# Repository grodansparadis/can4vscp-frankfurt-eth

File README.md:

<h1>CAN4VSCP Frankfurt Eth (PoE)</h1>

This work is based on original work done [here](https://github.com/nuclearcat/ESP32ETH). 

**Frankfurt Eth** is a tcp/ip and MQTT CAN4VSCP gateway. The module is available in two versions. One without PoE and and one with PoE.

The module is plug and play. Just connect to a CAN4VSCP system and go to work. You can connect to the module using [VSCP tcp/ip link protocol](https://grodansparadis.github.io/vscp-doc-spec/#/./vscp_tcpiplink) or set it up to talk to a MQTT broker of choice.

Note that this is **not** a CAN <-> tcp/ip (or MQTT) gateway as it only speaks [VSCP](https://grodansparadis.github.io/vscp-doc-spec). It is possible though to load firmware into it to create a standard CAN (not CAN FD) <-> tcp/ip gateway. 

The project uses an ESP32 Wroom module. It utilize Ethernet instead of Wifi/Bluetooth. Ethernet interface is provided with a LAN8720A and CAN is provided by the ESP32 support for TWAI. The module is powered from the [CAN4VSCP bus](https://grodansparadis.github.io/vscp-doc-spec/#/./vscp_over_can_can4vscp) (or PoE).  When powered from PoE the module can provide power for other CAN4VSCP modules. CAN4VSCP power is in the range +9V - 28V.

The intended use is to connect a remote CAN4VSCP bus to a central system or to connect two or more CAN4VSCP networks together. 

If Wifi is required instead of Ethernet the [CAN4VSCP Frankfurt Wifi module](https://github.com/grodansparadis/can4vscp-frankfurt-wifi) is available that can do that.

Prototype PCB's for this project has been sponsored by [PCBWay](https://www.pcbway.com/). We can really recommend this service if you need high quality PCB's. 

## Schema

### Standard version

### PoE version

## Standard version

## PoE Version

<hr>
Please support the <a href="http://www.vscp.org">VSCP development</a>. The best way to support the project is 
to buy something from the <a href="http://www.frogshop.se">FrogShop</a>. If you want to contribute money use the button
 at the end of the <a href="http://www.vscp.org">VSCP sites</a> start page.

Visit our <a href="http://www.vscp.org/wiki/doku.php/sponsors">sponsor page</a> for all options.

<hr>

Part of the VSCP Project.

Copyright 2018-2026 © Åke Hedman, (Grodans Paradis AB)[https://www.grodansparadis.com]

<hr>

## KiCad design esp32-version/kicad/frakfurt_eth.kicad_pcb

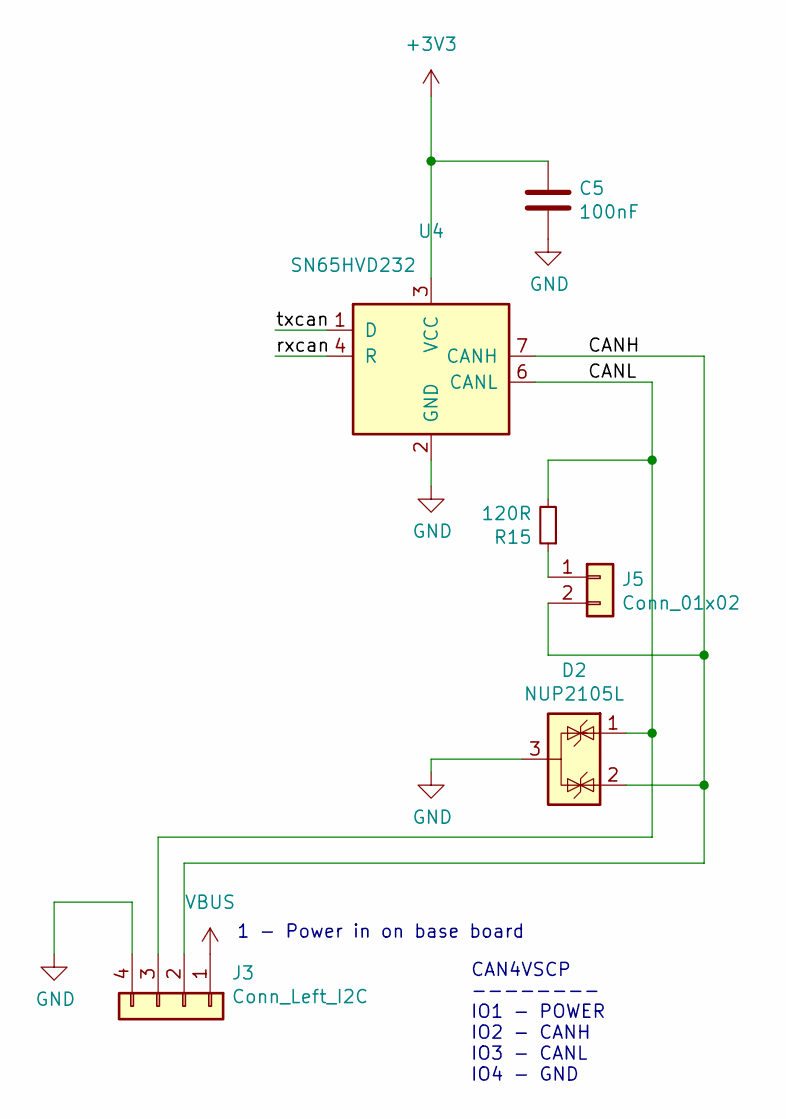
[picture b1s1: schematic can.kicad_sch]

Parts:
C5: 100nF; C_0805_2012Metric
D2: NUP2105L; SOT-23
J3: Conn_Left_I2C; PinHeader_1x04_P2.54mm_Vertical
J5: Conn_01x02; PinHeader_1x02_P2.54mm_Vertical
R15: 120R; R_0805_2012Metric
U4: SN65HVD232; SOIC-8_3.9x4.9mm_P1.27mm

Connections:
/CANH: D2.2 (K), J3.2, J5.2, U4.7 (CANH); also elsewhere on the board
/CANL: D2.1 (K), J3.3, R15.2, U4.6 (CANL); also elsewhere on the board
/rxcan: U4.4 (R); also elsewhere on the board
/txcan: U4.1 (D); also elsewhere on the board
GND: C5.2, D2.3 (A), J3.4, U4.2 (GND); also elsewhere on the board
unnamed: J5.1, R15.1

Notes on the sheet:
1 - Power in on base board
CAN4VSCP -------- IO1 - POWER IO2 - CANH IO3 - CANL IO4 - GND

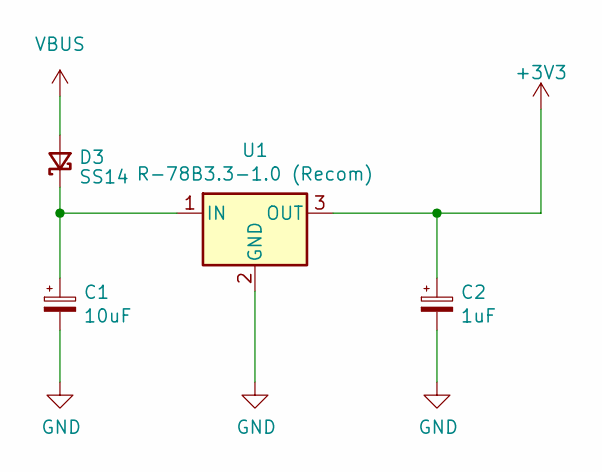
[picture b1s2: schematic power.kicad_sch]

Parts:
C1: 10uF; C_0805_2012Metric_Pad1.18x1.45mm_HandSolder
C2: 1uF; C_0805_2012Metric_Pad1.18x1.45mm_HandSolder
D3: SS14; D_SMA
U1: R-78B3.3-1.0 (Recom); Converter_DCDC_RECOM_R-78B-2.0_THT

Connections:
unnamed: C1.2, C2.2, U1.2 (GND)
unnamed: C2.1, U1.3 (OUT)
unnamed 31: C1.1, D3.1 (K), U1.1 (IN); also elsewhere on the board
VBUS: D3.2 (A); also elsewhere on the board

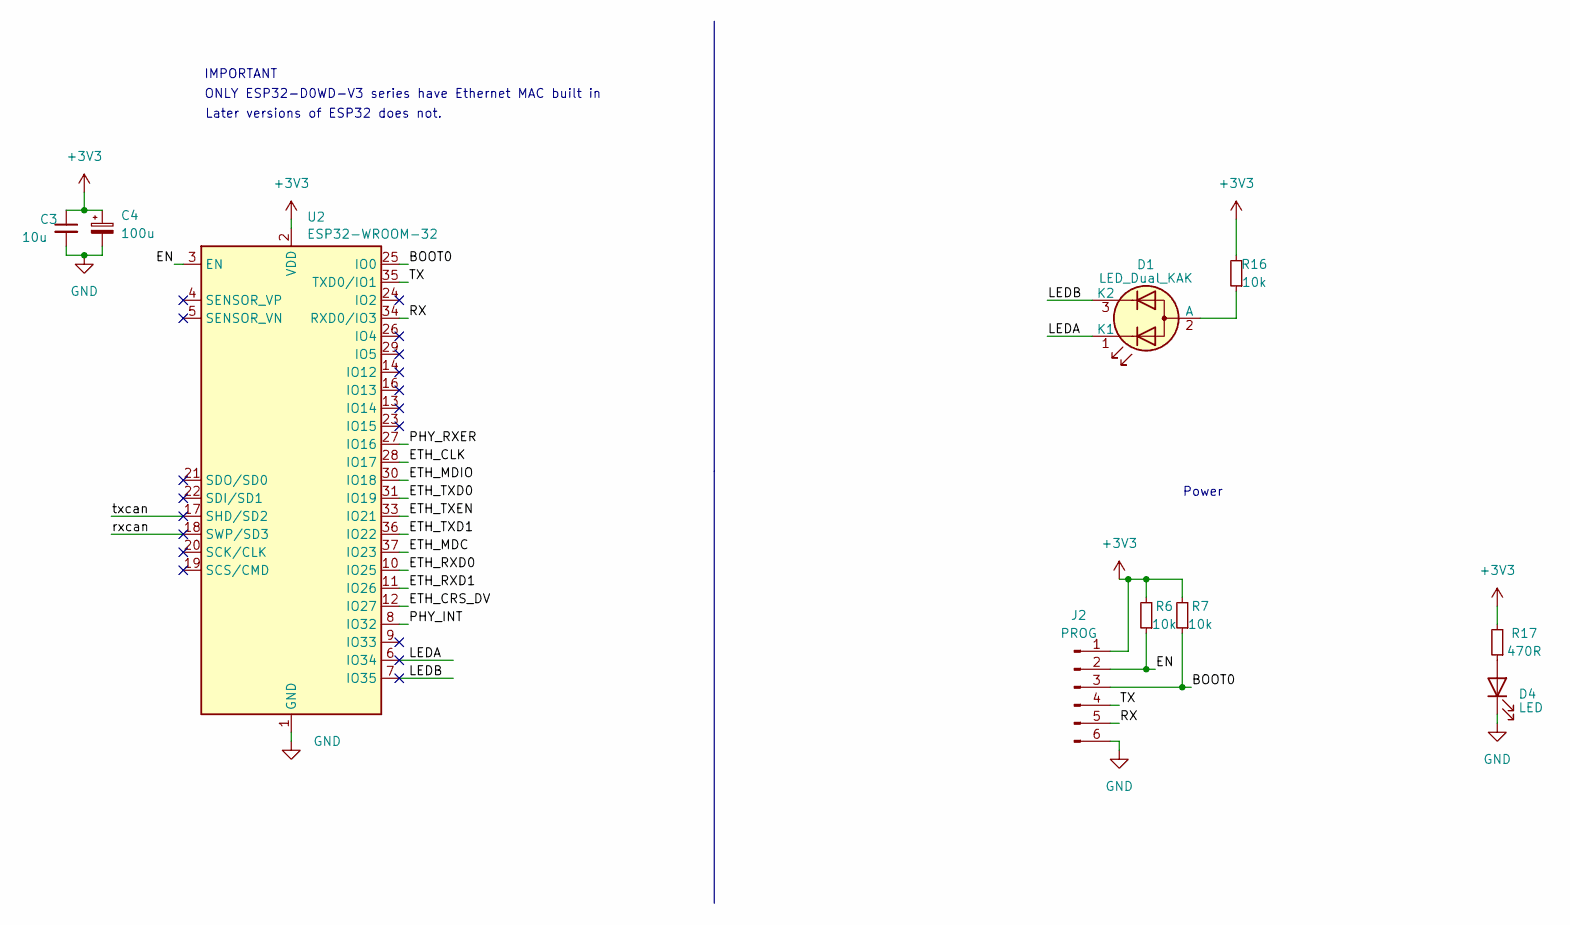
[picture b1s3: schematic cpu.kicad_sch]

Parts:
C3: 10u; C_0805_2012Metric_Pad1.18x1.45mm_HandSolder
C4: 100u; CP_EIA-3528-21_Kemet-B
D1: LED_Dual_KAK; LED_D5.0mm-3
D4: LED; LED_0805_2012Metric_Pad1.15x1.40mm_HandSolder
J2: PROG; PinHeader_1x06_P2.54mm_Vertical
R6, R7, R16: 10k; R_0805_2012Metric_Pad1.20x1.40mm_HandSolder
R17: 470R; R_0805_2012Metric_Pad1.20x1.40mm_HandSolder
U2: ESP32-WROOM-32

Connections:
/BOOT0: J2.3, R7.1, U2.25 (IO0)
/EN: J2.2, R6.1, U2.3 (EN)
/ETH_CLK: U2.28 (IO17); also elsewhere on the board
/ETH_CRS_DV: U2.12 (IO27); also elsewhere on the board
/ETH_MDC: U2.37 (IO23); also elsewhere on the board
/ETH_MDIO: U2.30 (IO18); also elsewhere on the board
/ETH_RXD0: U2.10 (IO25); also elsewhere on the board
/ETH_RXD1: U2.11 (IO26); also elsewhere on the board
/ETH_TXD0: U2.31 (IO19); also elsewhere on the board
/ETH_TXD1: U2.36 (IO22); also elsewhere on the board
/ETH_TXEN: U2.33 (IO21); also elsewhere on the board
/LEDA: D1.1 (K1), U2.6 (IO34)
/LEDB: D1.3 (K2), U2.7 (IO35)
/PHY_INT: U2.8 (IO32); also elsewhere on the board
/PHY_RXER: U2.27 (IO16); also elsewhere on the board
/RX: J2.5, U2.34 (RXD0/IO3)
/TX: J2.4, U2.35 (TXD0/IO1)
/rxcan: U2.18 (SWP/SD3); also elsewhere on the board
/txcan: U2.17 (SHD/SD2); also elsewhere on the board
GND: C3.2, C4.2, D4.1 (K), J2.6, U2.1 (GND), U2.15 (GND), U2.38 (GND), U2.39 (GND); also elsewhere on the board
unnamed: D1.2 (A), R16.1
unnamed: D4.2 (A), R17.1

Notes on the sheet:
Later versions of ESP32 does not.
ONLY ESP32-D0WD-V3 series have Ethernet MAC built in
IMPORTANT
Power

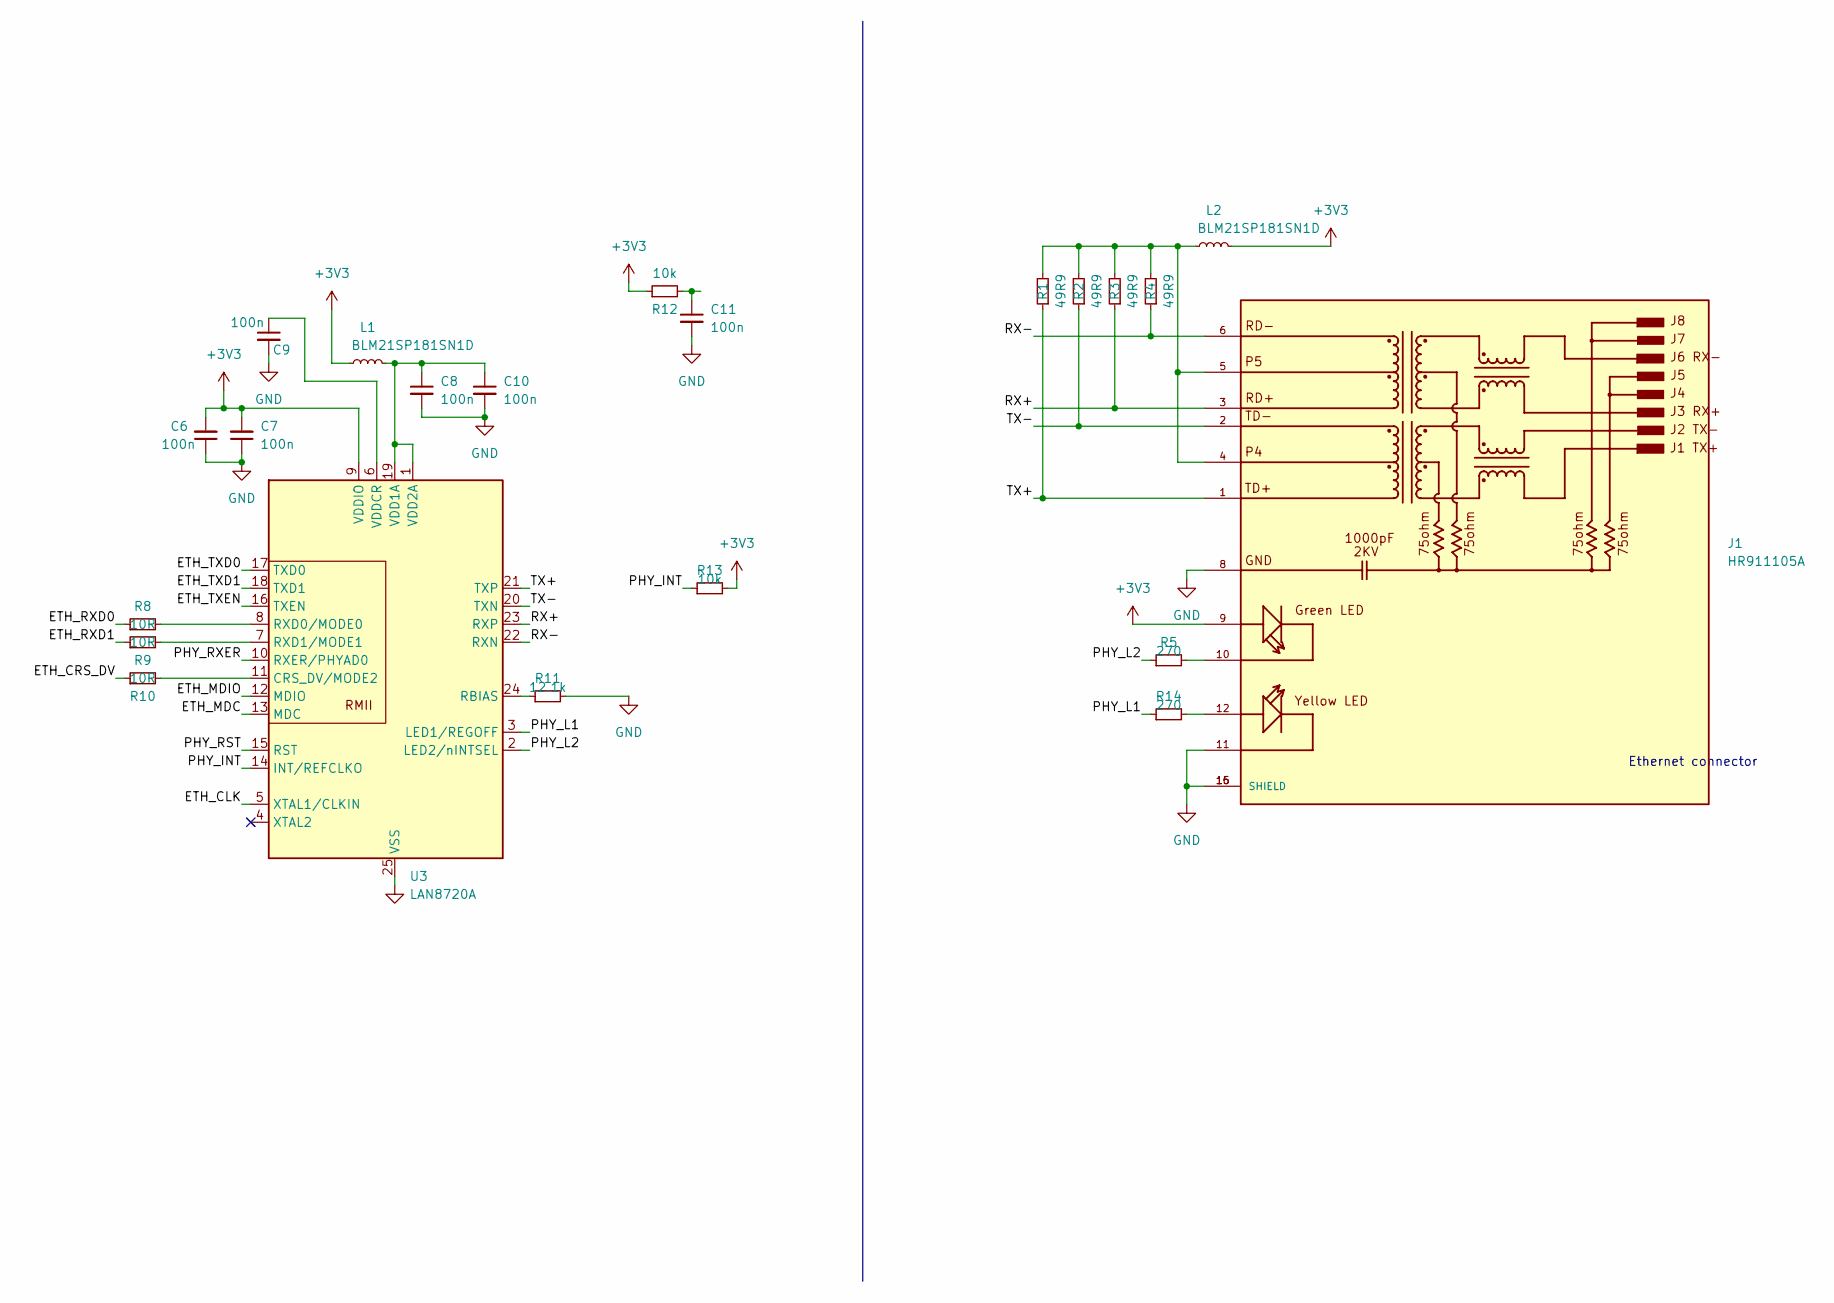
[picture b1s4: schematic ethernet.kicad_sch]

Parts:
C6, C7, C8, C9, C10, C11: 100n; C_0805_2012Metric_Pad1.18x1.45mm_HandSolder
J1: HR911105A; HANRUN_HR911105A; PARTREV A
L1, L2: BLM21SP181SN1D; R_0805_2012Metric_Pad1.20x1.40mm_HandSolder
R1, R2, R3, R4: 49R9; R_0805_2012Metric_Pad1.20x1.40mm_HandSolder
R5, R14: 270; R_0805_2012Metric_Pad1.20x1.40mm_HandSolder
R8, R9, R10: 10R; R_0805_2012Metric_Pad1.20x1.40mm_HandSolder
R11: 12.1k; R_0805_2012Metric_Pad1.20x1.40mm_HandSolder
R12, R13: 10k; R_0805_2012Metric_Pad1.20x1.40mm_HandSolder
U3: LAN8720A; QFN-24-1EP_4x4mm_P0.5mm_EP2.6x2.6mm

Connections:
/ETH_CLK: U3.5 (XTAL1/CLKIN); also elsewhere on the board
/ETH_CRS_DV: R10.1; also elsewhere on the board
/ETH_MDC: U3.13 (MDC); also elsewhere on the board
/ETH_MDIO: U3.12 (MDIO); also elsewhere on the board
/ETH_RXD0: R8.1; also elsewhere on the board
/ETH_RXD1: R9.1; also elsewhere on the board
/ETH_TXD0: U3.17 (TXD0); also elsewhere on the board
/ETH_TXD1: U3.18 (TXD1); also elsewhere on the board
/ETH_TXEN: U3.16 (TXEN); also elsewhere on the board
/PHY_INT: R13.1, U3.14 (INT/REFCLKO); also elsewhere on the board
/PHY_L1: R14.1, U3.3 (LED1/REGOFF)
/PHY_L2: R5.1, U3.2 (LED2/nINTSEL)
/PHY_RXER: U3.10 (RXER/PHYAD0); also elsewhere on the board
/RX+: J1.3, R3.1, U3.23 (RXP)
/RX-: J1.6, R4.1, U3.22 (RXN)
/TX+: J1.1, R1.1, U3.21 (TXP)
/TX-: J1.2, R2.1, U3.20 (TXN)
GND: C6.1, C7.1, C8.2, C9.2, C10.2, C11.2, J1.8, J1.11, J1.15 (SHIELD), J1.16 (SHIELD), R11.2, U3.25 (VSS); also elsewhere on the board
unnamed: J1.10, R5.2
unnamed: J1.12, R14.2
unnamed: R10.2, U3.11 (CRS_DV/MODE2)
unnamed: R11.1, U3.24 (RBIAS)
unnamed: R8.2, U3.8 (RXD0/MODE0)
unnamed: R9.2, U3.7 (RXD1/MODE1)
unnamed: C8.1, C10.1, L1.2, U3.1 (VDD2A), U3.19 (VDD1A)
unnamed: C9.1, U3.6 (VDDCR)

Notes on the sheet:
Ethernet connector

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
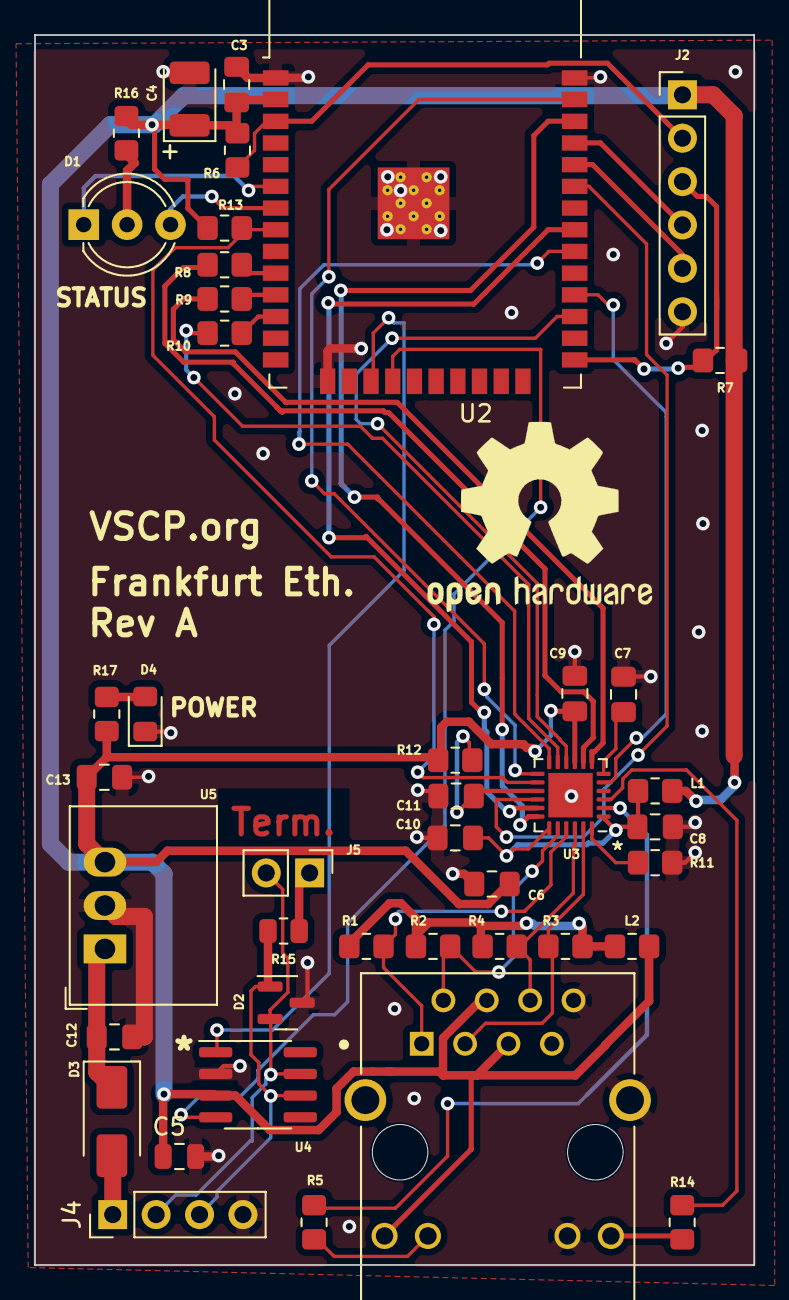
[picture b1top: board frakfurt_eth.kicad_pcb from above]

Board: 2 copper layers, 42.1 x 72.0 mm, 42 parts (0 on the bottom side), 44 nets.

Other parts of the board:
C12: 10uF; C_0805_2012Metric_Pad1.18x1.45mm_HandSolder
C13: 1uF; C_0805_2012Metric_Pad1.18x1.45mm_HandSolder
J4: Conn_Left_I2C; PinHeader_1x04_P2.54mm_Vertical
U5: R-78B3.3-1.0 (Recom); Converter_DCDC_RECOM_R-78B-2.0_THT

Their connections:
/CANH: J4.2; also elsewhere on the board
/CANL: J4.3; also elsewhere on the board
GND: C12.2, C13.2, J4.4, U5.2 (GND); also elsewhere on the board
unnamed 31: C12.1, U5.1 (IN); also elsewhere on the board
VBUS: J4.1; also elsewhere on the board

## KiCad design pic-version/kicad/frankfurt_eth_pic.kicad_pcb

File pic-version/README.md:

# Microchip PIC Version

This is an old version of this project that is no longer maintained.

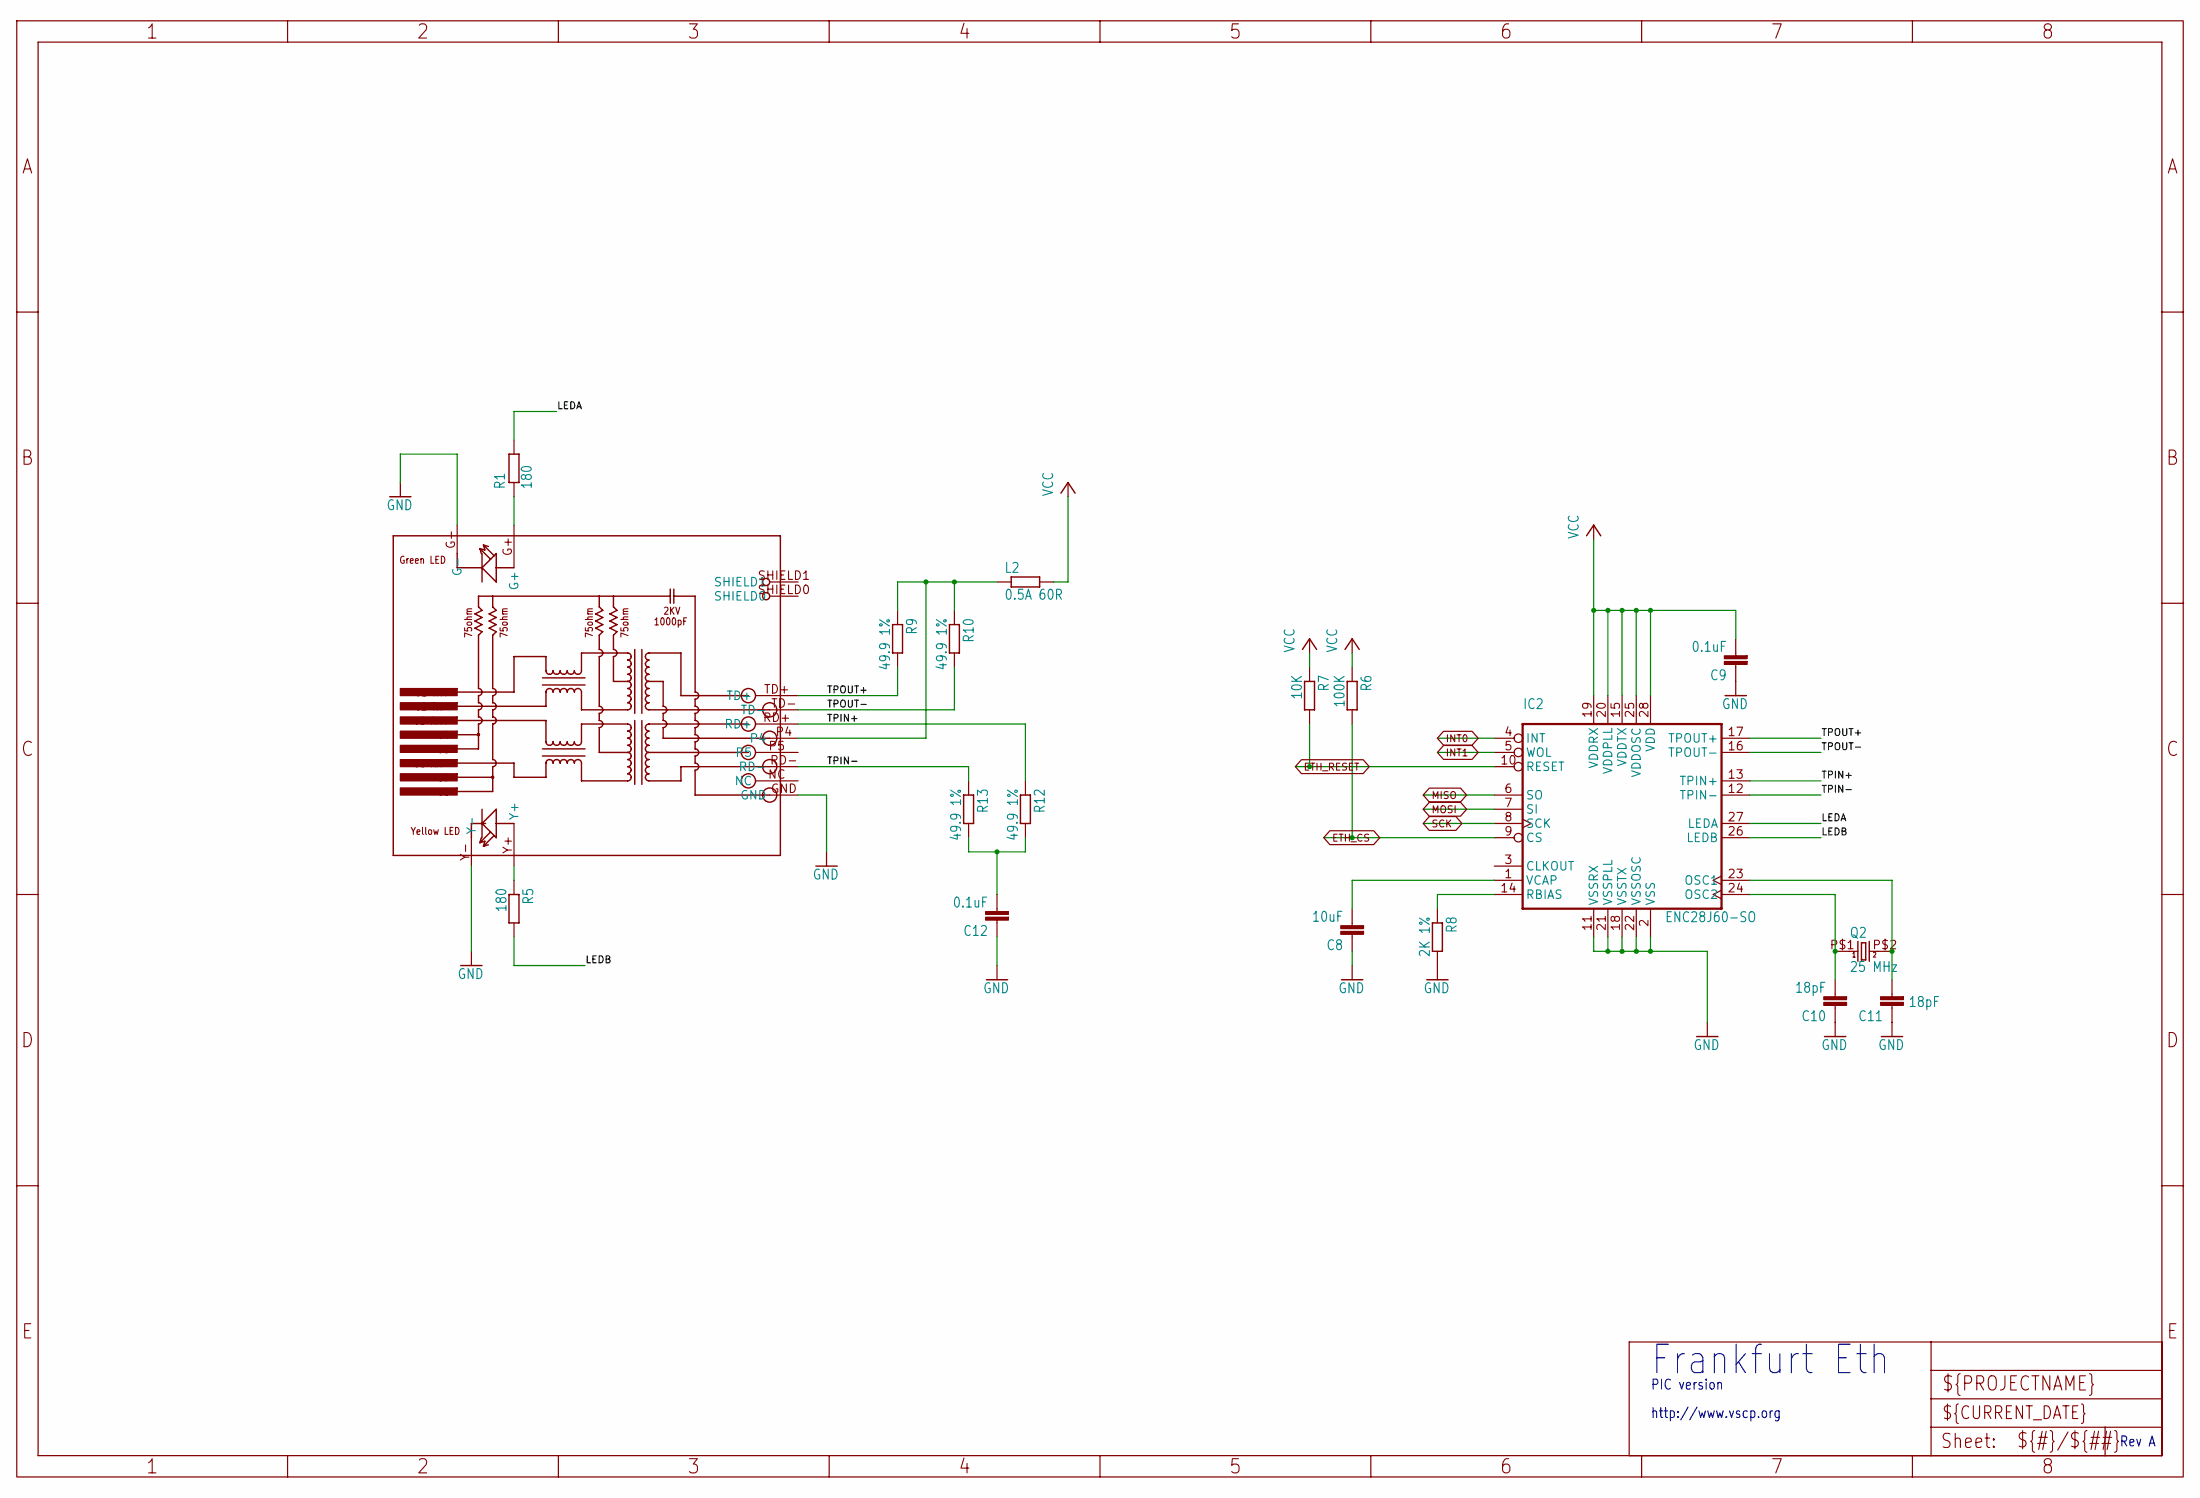
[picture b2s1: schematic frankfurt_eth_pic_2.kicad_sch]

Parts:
C8: 10uF; C0805
C9, C12: 0.1uF; C0805
C10, C11: 18pF; C0805
IC2: ENC28J60-SO; SO28W
L2: 0.5A 60R; R0805
Q2: 25 MHz; 9C
R1, R5: 180; R0805
R6: 100K; R0805
R7: 10K; R0805
R8: 2K 1%; R0805
R9, R10, R12, R13: 49.9 1%; R0805
RJ1: HR911105A

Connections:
ETH_CS: IC2.9 (CS), R6.2; also elsewhere on the board
ETH_RESET: IC2.10 (RESET), R7.2; also elsewhere on the board
GND: C8.1, C9.1, C10.1, C11.1, C12.1, IC2.2 (VSS), IC2.11 (VSSRX), IC2.18 (VSSTX), IC2.21 (VSSPLL), IC2.22 (VSSOSC), R8.2, RJ1.G-, RJ1.GND, RJ1.Y-; also elsewhere on the board
INT0: IC2.4 (INT); also elsewhere on the board
INT1: IC2.5 (WOL); also elsewhere on the board
LEDA: IC2.27 (LEDA), R1.2
LEDB: IC2.26 (LEDB), R5.2
MISO: IC2.6 (SO); also elsewhere on the board
MOSI: IC2.7 (SI); also elsewhere on the board
unnamed: R1.1, RJ1.G+
unnamed: C8.2, IC2.1 (VCAP)
unnamed: R5.1, RJ1.Y+
unnamed: IC2.14 (RBIAS), R8.1
unnamed: C10.2, IC2.24 (OSC2), Q2.P$1 (1)
unnamed: C11.2, IC2.23 (OSC1), Q2.P$2 (2)
unnamed: C12.2, R12.2, R13.2
unnamed: L2.1, R9.1, R10.1, RJ1.P4
SCK: IC2.8 (SCK); also elsewhere on the board
TPIN+: IC2.13 (TPIN+), R12.1, RJ1.RD+
TPIN-: IC2.12 (TPIN-), R13.1, RJ1.RD-
TPOUT+: IC2.17 (TPOUT+), R9.2, RJ1.TD+
TPOUT-: IC2.16 (TPOUT-), R10.2, RJ1.TD-
VCC: C9.2, IC2.15 (VDDTX), IC2.19 (VDDRX), IC2.20 (VDDPLL), IC2.25 (VDDOSC), IC2.28 (VDD), L2.2, R6.1, R7.1; also elsewhere on the board

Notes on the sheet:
Rev A
Frankfurt Eth
PIC version
http://www.vscp.org

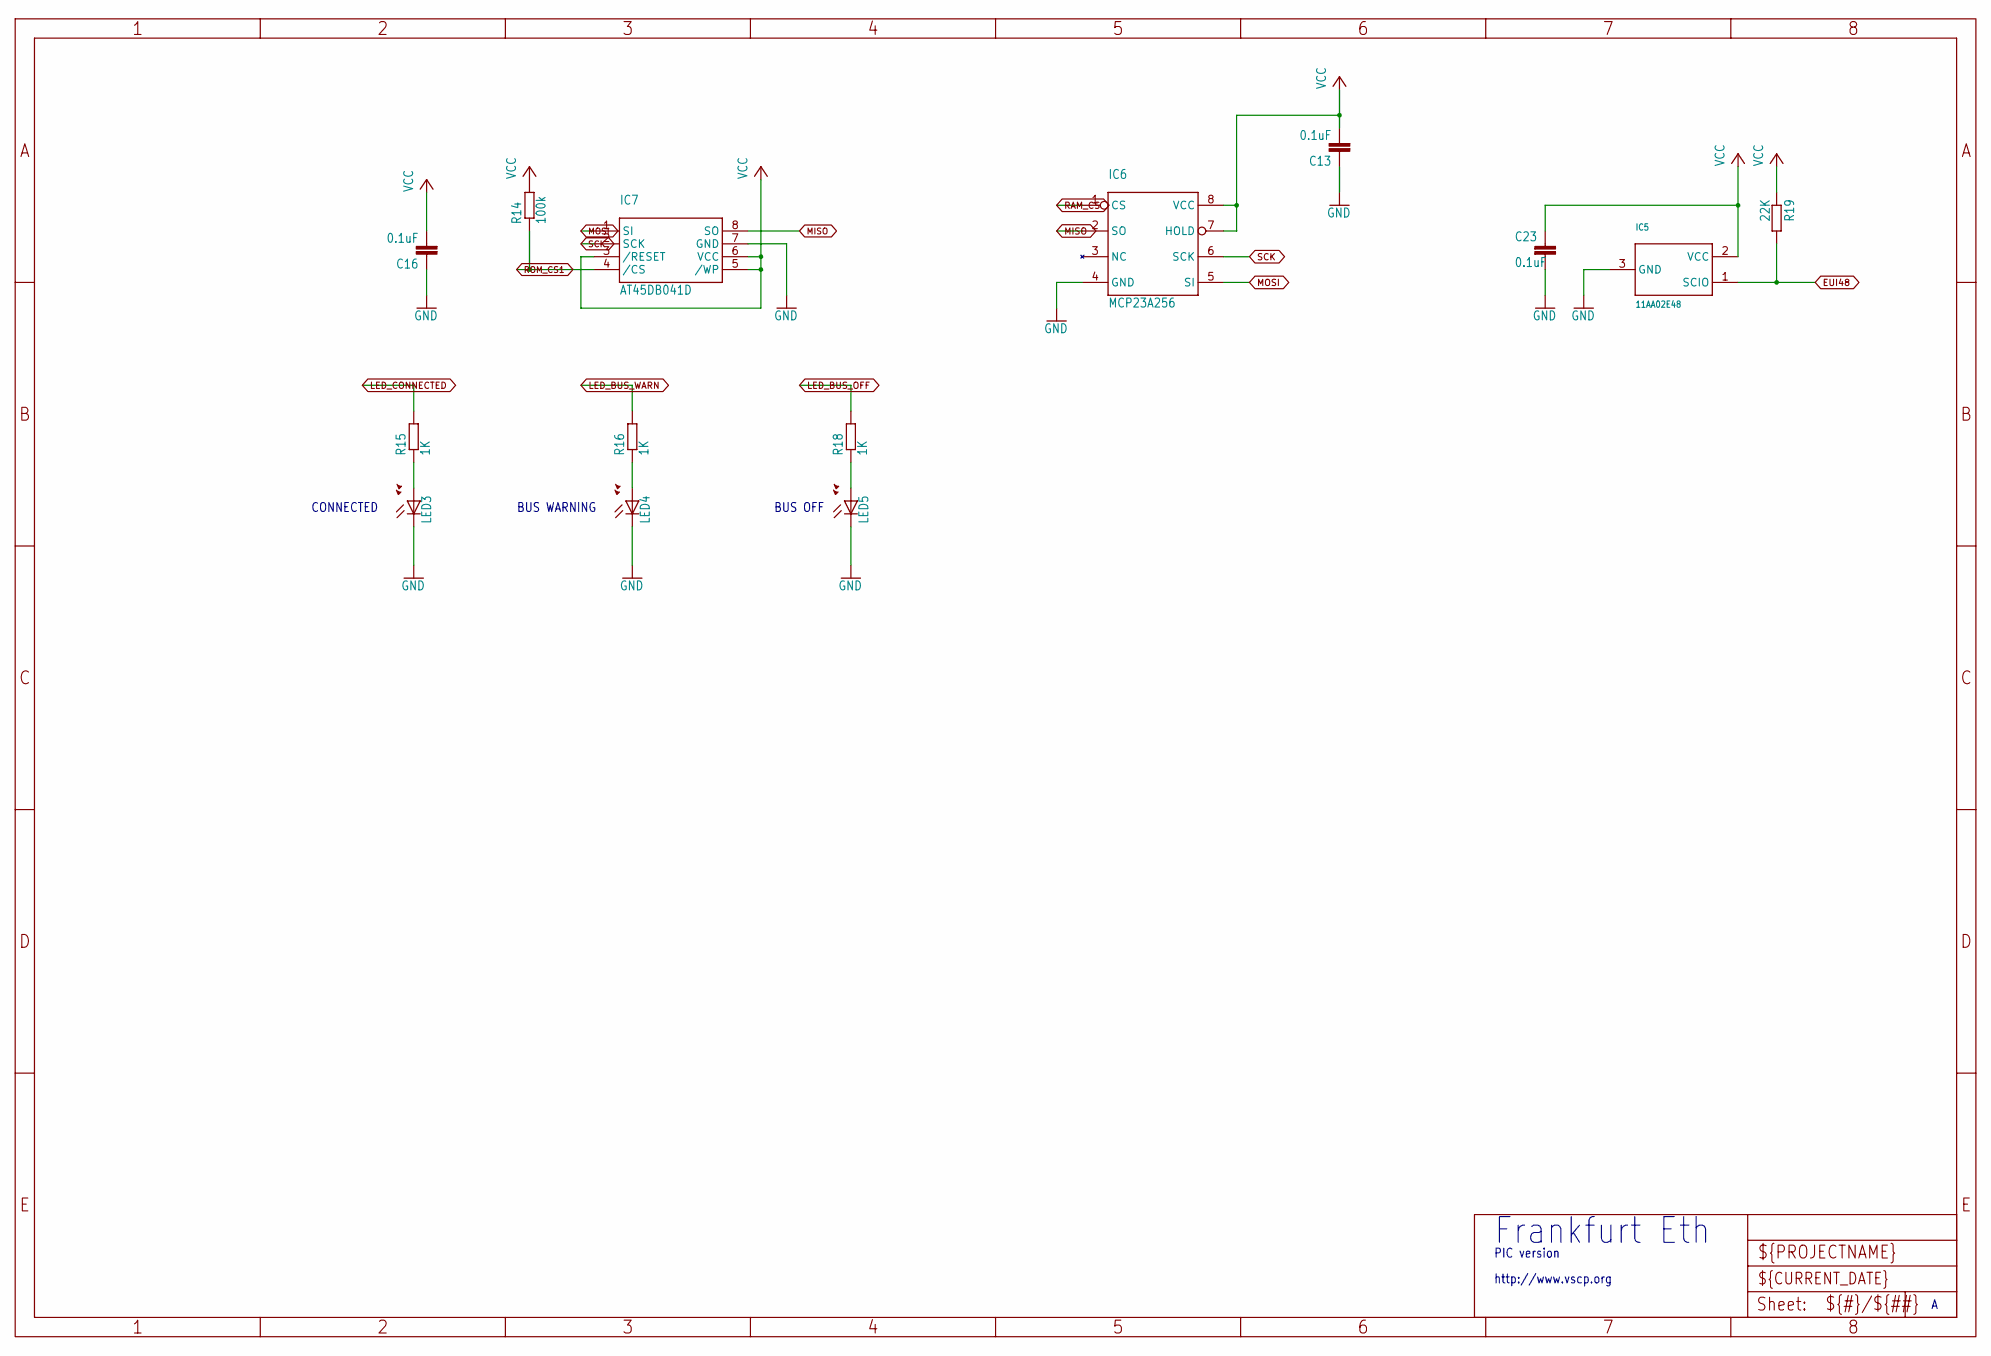
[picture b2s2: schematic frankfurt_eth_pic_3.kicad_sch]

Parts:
C13, C16, C23: 0.1uF; C0805
IC5: 11AA02E48; SOT23
IC6: MCP23A256; SO-8
IC7: AT45DB041D; SOP8W
LED3, LED4, LED5: LEDCHIP-LED0805; CHIP-LED0805
R14: 100k; M0805
R15, R16, R18: 1K; R0805
R19: 22K; M0805

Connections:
EUI48: IC5.1 (SCIO), R19.2; also elsewhere on the board
GND: C13.1, C16.1, C23.2, IC5.3 (GND), IC6.4 (GND), IC7.7 (GND), LED3.C, LED4.C, LED5.C; also elsewhere on the board
LED_BUS_OFF: R18.2; also elsewhere on the board
LED_BUS_WARN: R16.2; also elsewhere on the board
LED_CONNECTED: R15.2; also elsewhere on the board
MISO: IC6.2 (SO), IC7.8 (SO); also elsewhere on the board
MOSI: IC6.5 (SI), IC7.1 (SI); also elsewhere on the board
unnamed: LED3.A, R15.1
unnamed: LED4.A, R16.1
unnamed: LED5.A, R18.1
RAM_CS: IC6.1 (CS); also elsewhere on the board
ROM_CS1: IC7.4 (/CS), R14.1; also elsewhere on the board
SCK: IC6.6 (SCK), IC7.2 (SCK); also elsewhere on the board
VCC: C13.2, C16.2, C23.1, IC5.2 (VCC), IC6.7 (HOLD), IC6.8 (VCC), IC7.3 (/RESET), IC7.5 (/WP), IC7.6 (VCC), R14.2, R19.1; also elsewhere on the board

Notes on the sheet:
BUS OFF
PIC version
http://www.vscp.org
CONNECTED
BUS WARNING
Frankfurt Eth

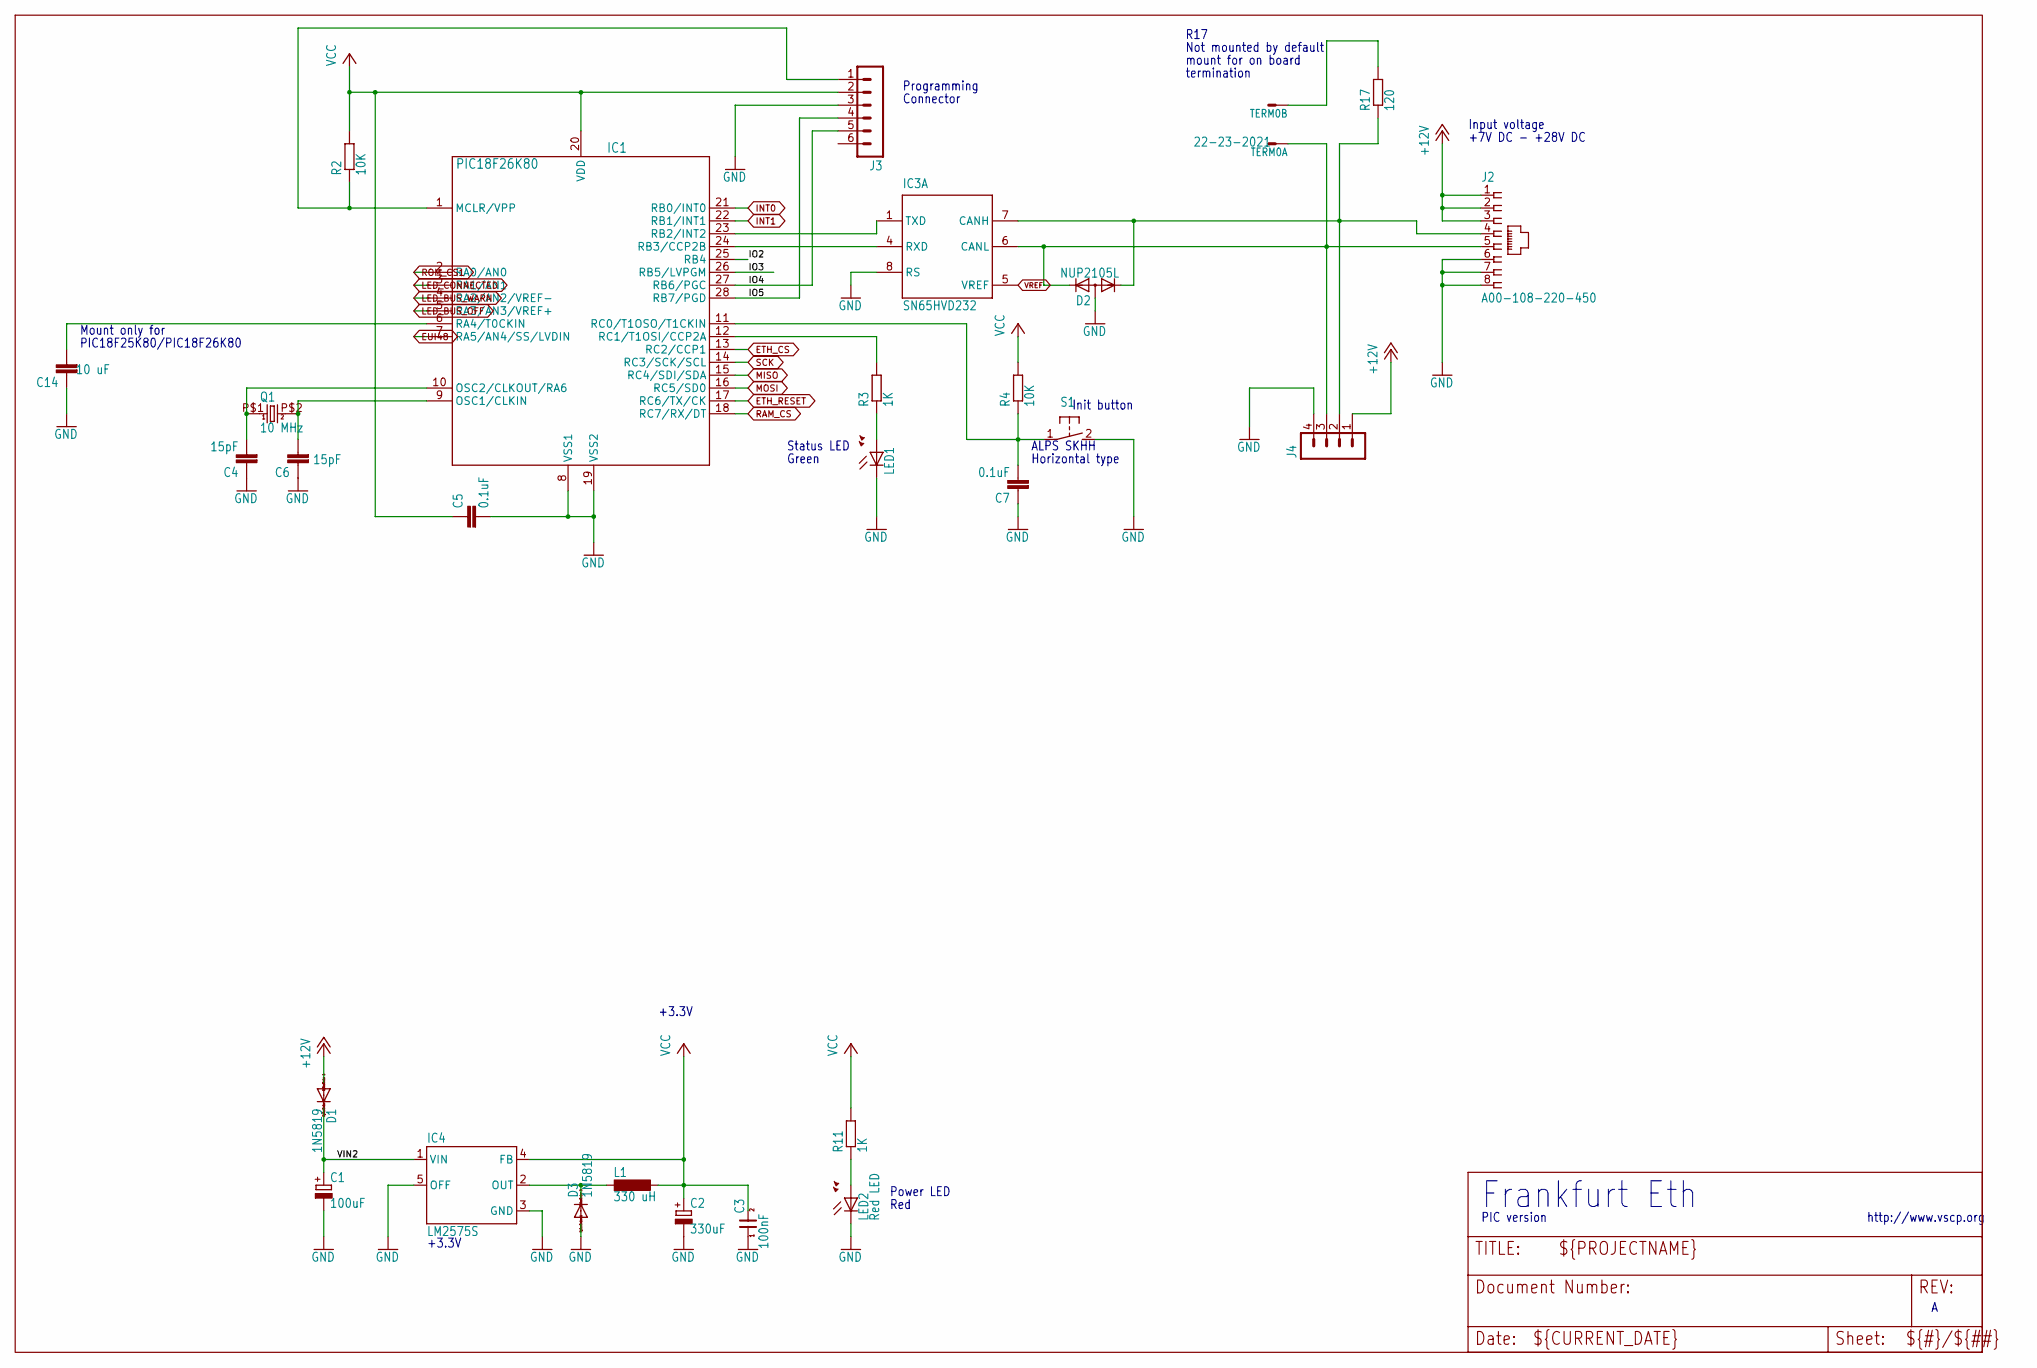
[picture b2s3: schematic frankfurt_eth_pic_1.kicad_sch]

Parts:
C1: 100uF; PANASONIC_D
C2: 330uF; PANASONIC_D
C3: 100nF; 0805
C4, C6: 15pF; C0805
C5, C7: 0.1uF; C0805
C14: 10 uF; C0805
D1, D3: 1N5819; SOD123
D2: NUP2105L; SOT23
IC1: PIC18F26K80; SO28
IC3: SN65HVD232; SO-08
IC4: LM2575S; TO263-5
J2: A00-108-220-450; RJ-45
J3: MA06-1
J4: MA04-1
L1: 330 uH; DO3316P
LED1: LEDCHIP-LED0805; CHIP-LED0805
LED2: Red LED; CHIP-LED0805
Q1: 10 MHz; 9C
R2, R4: 10K; R0805
R3, R11: 1K; R0805
R17: 120; R0805
S1: 31-XX; B3F-31XX
TERM0: 22-23-2021

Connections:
+12V: D1.A, J2.1, J2.2, J2.3, J4.1
CANL: D2.2 (K2), IC3.6 (CANL), J2.5, J4.3, TERM0.1
ETH_CS: IC1.13 (RC2/CCP1); also elsewhere on the board
ETH_RESET: IC1.17 (RC6/TX/CK); also elsewhere on the board
EUI48: IC1.7 (RA5/AN4/SS/LVDIN); also elsewhere on the board
GND: C1.-, C2.-, C3.1, C4.1, C5.2, C6.1, C7.1, C14.1, D2.3 (A), D3.A, IC1.8 (VSS1), IC1.19 (VSS2), IC3.2 (VSS), IC3.8 (RS), IC4.3 (GND), IC4.5 (OFF), J2.6, J2.7, J2.8, J3.3, J4.4, LED1.C, LED2.C, S1.2 (S); also elsewhere on the board
INT0: IC1.21 (RB0/INT0); also elsewhere on the board
INT1: IC1.22 (RB1/INT1); also elsewhere on the board
IO2: IC1.25 (RB4)
IO3: IC1.26 (RB5/LVPGM)
IO4: IC1.27 (RB6/PGC), J3.5
IO5: IC1.28 (RB7/PGD), J3.4
LED_BUS_OFF: IC1.5 (RA3/AN3/VREF+); also elsewhere on the board
LED_BUS_WARN: IC1.4 (RA2/AN2/VREF-); also elsewhere on the board
LED_CONNECTED: IC1.3 (RA1/AN1); also elsewhere on the board
MISO: IC1.15 (RC4/SDI/SDA); also elsewhere on the board
MOSI: IC1.16 (RC5/SD0); also elsewhere on the board
unnamed: D3.C, IC4.2 (OUT), L1.1
unnamed: C4.2, IC1.10 (OSC2/CLKOUT/RA6), Q1.P$1 (1)
unnamed: C14.2, IC1.6 (RA4/T0CKIN)
unnamed: IC1.12 (RC1/T1OSI/CCP2A), R3.2
unnamed: LED1.A, R3.1
unnamed: C7.2, IC1.11 (RC0/T1OSO/T1CKIN), R4.1, S1.1
unnamed: C6.2, IC1.9 (OSC1/CLKIN), Q1.P$2 (2)
unnamed: R17.2, TERM0.2
unnamed: LED2.A, R11.1
unnamed: D2.1 (K1), IC3.7 (CANH), J2.4, J4.2, R17.1
RAM_CS: IC1.18 (RC7/RX/DT); also elsewhere on the board
RESET: IC1.1 (MCLR/VPP), J3.1, R2.1
ROM_CS1: IC1.2 (RA0/AN0); also elsewhere on the board
RXCAN: IC1.24 (RB3/CCP2B), IC3.4 (RXD)
SCK: IC1.14 (RC3/SCK/SCL); also elsewhere on the board
TXCAN: IC1.23 (RB2/INT2), IC3.1 (TXD)
VCC: C2.+, C3.2, C5.1, IC1.20 (VDD), IC3.3 (VDD), IC4.4 (FB), J3.2, L1.2, R2.2, R4.2, R11.2; also elsewhere on the board
VIN2: C1.+, D1.C, IC4.1 (VIN)
VREF: IC3.5 (VREF)

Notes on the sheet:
Power LED
Status LED
Frankfurt Eth
PIC version
Mount only for
http://www.vscp.org
Not mounted by default
PIC18F25K80/PIC18F26K80
Horizontal type
mount for on board
R17
Red
Programming
ALPS SKHH
termination
+3.3V
Connector
Green
Init button
Input voltage
+7V DC - +28V DC
